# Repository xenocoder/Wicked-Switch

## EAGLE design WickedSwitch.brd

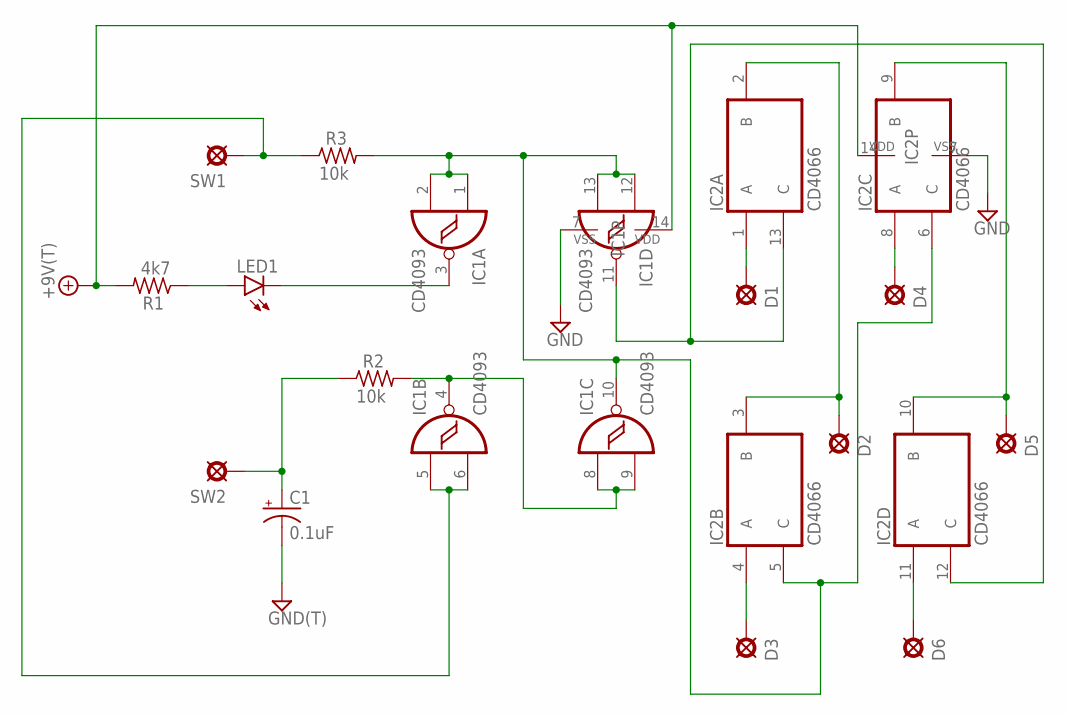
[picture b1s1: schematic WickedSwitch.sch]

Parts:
+9V: +9V(T); SQUARE
C1: 0.1uF; 050_020_1
D1, D2, D3, D4, D5, D6: 1; ROUND
GND: GND(T); SQUARE
IC1: CD4093; DIL14
IC2: CD4066; DIL14
LED1: LED3MM
R1: 4k7; R0207/3
R2, R3: 10k; R0207/3
SW1, SW2: 1; ROUND

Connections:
+9V: +9V.1, IC1.14 (VDD), IC2.14 (VDD), R1.2
GND: C1.-, GND.1, IC1.7 (VSS), IC2.7 (VSS)
unnamed: C1.+, R2.1, SW2.1
unnamed: D1.1, IC2.1 (A)
unnamed: LED1.A, R1.1
unnamed: IC1.3 (O), LED1.K (C)
unnamed: IC1.5 (I0), IC1.6 (I1), R3.1, SW1.1
unnamed: IC1.4 (O), IC1.8 (I0), IC1.9 (I1), R2.2
unnamed: D2.1, IC2.2 (B), IC2.3 (B)
unnamed: IC1.11 (O), IC2.12 (C), IC2.13 (C)
unnamed: IC1.1 (I0), IC1.2 (I1), IC1.10 (O), IC1.12 (I0), IC1.13 (I1), IC2.5 (C), IC2.6 (C), R3.2
unnamed: D3.1, IC2.4 (A)
unnamed: D4.1, IC2.8 (A)
unnamed: D5.1, IC2.9 (B), IC2.10 (B)
unnamed: D6.1, IC2.11 (A)

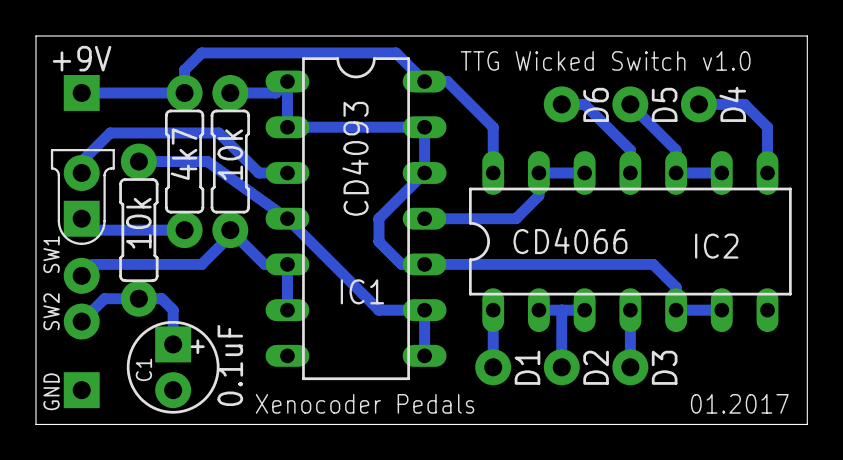
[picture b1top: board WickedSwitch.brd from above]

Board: 2 copper layers, 42.9 x 21.6 mm, 17 parts (0 on the bottom side), 15 nets.

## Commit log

2017-01-04 First Commit for all files for Version 1.0 going to OSHPark
2017-01-04 Redo Version 1.0 to put values on silkscreen
2017-01-13 Added gerber files for v1.0
